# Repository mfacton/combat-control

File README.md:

# combat-control
All in one combat robot controller

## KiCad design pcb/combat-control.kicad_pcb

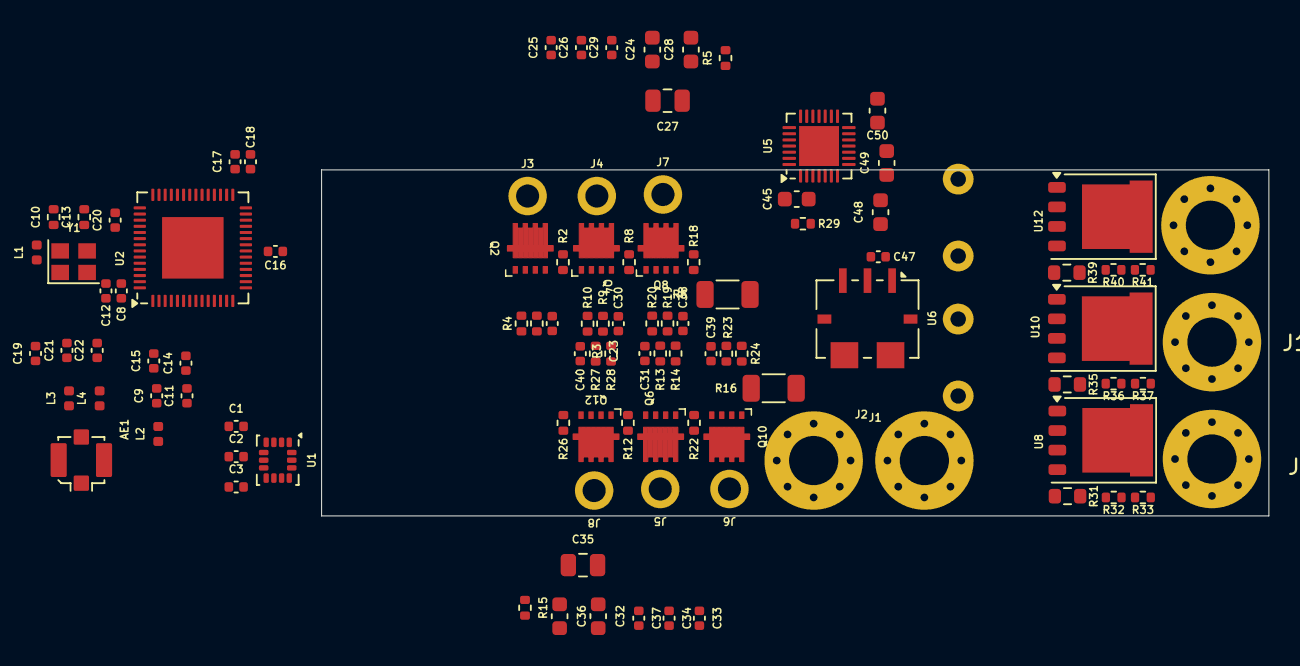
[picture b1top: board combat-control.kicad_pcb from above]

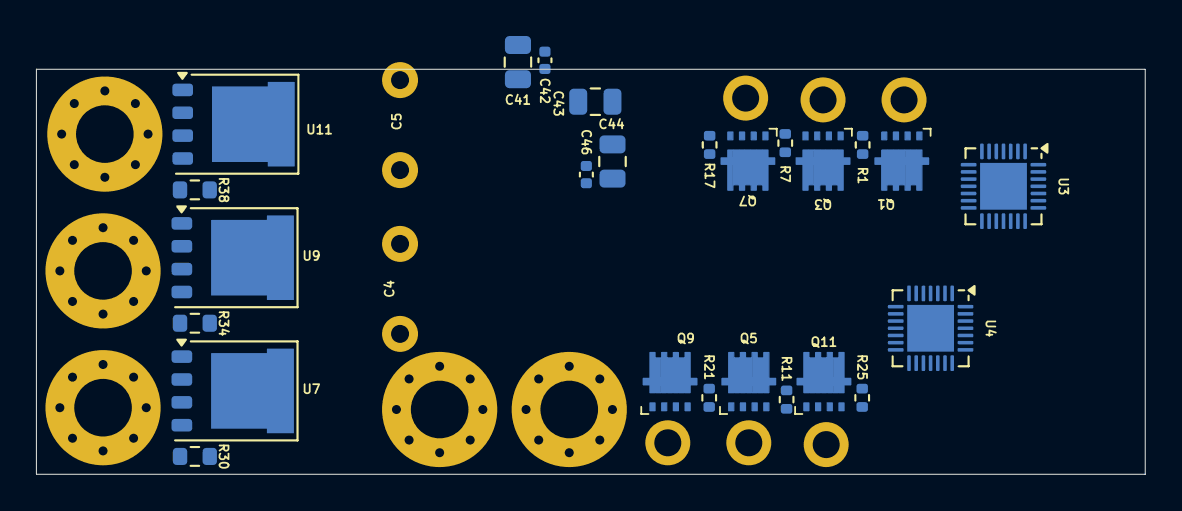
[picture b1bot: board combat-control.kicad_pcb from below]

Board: 4 copper layers, 61.6 x 22.5 mm, 130 parts (27 on the bottom side), 91 nets, no tracks yet.

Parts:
AE1: Antenna_Shield; U.FL_Molex_MCRF_73412-0110_Vertical
C1: 4u7; C_0402_1005Metric
C2, C3, C14, C15, C16, C17, C20, C25, C29, C33, C37, C42, C46, C47: 100n; C_0402_1005Metric
C4, C5: 2m2; C_D10xL16_Horizontal
C8, C11, C18, C23, C30, C31, C38, C39, C40: 1u; C_0402_1005Metric
C9: 10u; C_0402_1005Metric
C10, C13: C; R_0402_1005Metric
C12: 10n; C_0402_1005Metric
C19, C21, C22, C26, C34: C; C_0402_1005Metric
C24, C32, C48, C49, C50: 10u; C_0603_1608Metric
C27, C35, C43, C44: 10u; C_0805_2012Metric
C28, C36, C45: 470n; C_0603_1608Metric
C41: 22u; C_0805_2012Metric
J1, J2, J9, J10, J11: Conn_01x01_Pin; MountingHole_3.2mm_M3_Pad_Via
J3, J4, J5, J6, J7, J8: Conn_01x01_Pin; Pad-P1.5
L1, L3, L4: L; L_0402_1005Metric
L2: 2nH; L_0402_1005Metric
Q1, Q2, Q3, Q4, Q5, Q6, Q7, Q8, Q9, Q10, Q11, Q12: AON7544; DFN3x3A_8L_EP1_P
R1, R2, R7, R8, R11, R12, R17, R18, R21, R22, R25, R26: 22R; R_0402_1005Metric
R3, R9, R13, R19, R23, R27: 4k7; R_0402_1005Metric
R4, R10, R14, R20, R24, R28: 1k; R_0402_1005Metric
R5, R15: R; R_0402_1005Metric
R6, R16: 2m; R_1206_3216Metric
R29: 10k; R_0402_1005Metric
R30, R31, R34, R35, R38, R39: 22R; R_0603_1608Metric
R32, R36, R40: 15k; R_0402_1005Metric
R33, R37, R41: 2k; R_0402_1005Metric
U1: ICM-42688-P; LGA-14_3x2.5mm_P0.5mm_LayoutBorder3x4y
U2: ESP32-S3; QFN-56-1EP_7x7mm_P0.4mm_EP4x4mm
U3, U4, U5: DRV8328B; QFN-28-1EP_4x4mm_P0.4mm_EP2.6x2.6mm
U6: ACS781xLRTR-100B; Allegro_PSOF-7_4.8x6.4mm_P1.60mm
U7, U8, U9, U10, U11, U12: TPHR8504PL; PQFN-8-EP_6x5mm_P1.27mm_Generic
Y1: 40MHz; Crystal_SMD_2520-4Pin_2.5x2.0mm

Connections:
+3V3: C1.1, C2.1, C3.1, C8.1, C9.1, C11.1, C12.1, C14.1, C16.1, C17.1, C18.1, C20.1, C47.1, L2.1, U1.5 (VDDIO), U1.8 (VDD), U2.4 (CHIP_PU), U2.20 (VDD3P3_RTC), U2.29 (VDD_SPI), U2.46 (VDD3P3_CPU), U2.55 (VDDA), U2.56 (VDDA), U3.21 (INLC), U3.22 (INLB), U3.23 (INLA), U3.25 (~SLP), U4.21 (INLC), U4.22 (INLB), U4.23 (INLA), U4.25 (~SLP), U5.21 (INLC), U5.22 (INLB), U5.23 (INLA), U5.26 (DLVL), U6.1 (VCC)
/IFIG: U2.5 (GPIO0), U2.51 (GPIO45)
/ILIM: C26.1, C34.1, R5.1, R15.1
/LargeMotor/BSTA: C48.1, U5.5 (BSTA)
/LargeMotor/BSTB: C49.1, U5.9 (BSTB)
/LargeMotor/BSTC: C50.1, U5.13 (BSTC)
/LargeMotor/GVDD: C41.1, C42.1, U5.4 (GVDD)
/LargeMotor/HIA: R30.1, U5.7 (GHA)
/LargeMotor/HIB: R34.1, U5.11 (GHB)
/LargeMotor/HIC: R38.1, U5.15 (GHC)
/LargeMotor/LOA: R31.1, U5.8 (GLA)
/LargeMotor/LOB: R35.1, U5.12 (GLB)
/LargeMotor/LOC: R39.1, U5.16 (GLC)
/LargeMotor/LOW: C4.2, C5.1, U6.6 (IP-), U8.1 (S), U8.2 (S), U8.3 (S), U10.1 (S), U10.2 (S), U10.3 (S), U12.1 (S), U12.2 (S), U12.3 (S)
/LargeMotor/OUTA: C48.2, J9.1, R32.1, U5.6 (SHA), U7.1 (S), U7.2 (S), U7.3 (S), U8.5 (D)
/LargeMotor/OUTB: C49.2, J10.1, R36.1, U5.10 (SHB), U9.1 (S), U9.2 (S), U9.3 (S), U10.5 (D)
/LargeMotor/OUTC: C50.2, J11.1, R40.1, U5.14 (SHC), U11.1 (S), U11.2 (S), U11.3 (S), U12.5 (D)
/SNSA1: R3.2, R4.1
/SNSA2: R23.2, R24.1
/SNSA3: R32.2, R33.1
/SNSB1: R9.2, R10.1
/SNSB2: R13.2, R14.1
/SNSB3: R36.2, R37.1
/SNSC1: R19.2, R20.1
/SNSC2: R27.2, R28.1
/SNSC3: R40.2, R41.1
/STP: U2.8 (GPIO3), U2.52 (GPIO46)
/SmallMotor1/BSTA: C23.1, U3.5 (BSTA)
/SmallMotor1/BSTB: C30.1, U3.9 (BSTB)
/SmallMotor1/BSTC: C38.1, U3.13 (BSTC)
/SmallMotor1/DL: R5.2, U3.26 (DLVL)
/SmallMotor1/GVDD: C24.1, C25.1, U3.4 (GVDD)
/SmallMotor1/HIA: R1.1, U3.7 (GHA)
/SmallMotor1/HIB: R7.1, U3.11 (GHB)
/SmallMotor1/HIC: R17.1, U3.15 (GHC)
/SmallMotor1/LOA: R2.1, U3.8 (GLA)
/SmallMotor1/LOB: R8.1, U3.12 (GLB)
/SmallMotor1/LOC: R18.1, U3.16 (GLC)
/SmallMotor1/LOW: Q2.1 (S), Q2.2 (S), Q2.3 (S), Q4.1 (S), Q4.2 (S), Q4.3 (S), Q8.1 (S), Q8.2 (S), Q8.3 (S), R6.1, U3.17 (LSS)
/SmallMotor1/OUTA: C23.2, J3.1, Q1.1 (S), Q1.2 (S), Q1.3 (S), Q2.5 (D), Q2.6 (D), Q2.7 (D), Q2.8 (D), R3.1, U3.6 (SHA)
/SmallMotor1/OUTB: C30.2, J4.1, Q3.1 (S), Q3.2 (S), Q3.3 (S), Q4.5 (D), Q4.6 (D), Q4.7 (D), Q4.8 (D), R9.1, U3.10 (SHB)
/SmallMotor1/OUTC: C38.2, J7.1, Q7.1 (S), Q7.2 (S), Q7.3 (S), Q8.5 (D), Q8.6 (D), Q8.7 (D), Q8.8 (D), R19.1, U3.14 (SHC)
/SmallMotor2/BSTA: C39.1, U4.5 (BSTA)
/SmallMotor2/BSTB: C31.1, U4.9 (BSTB)
/SmallMotor2/BSTC: C40.1, U4.13 (BSTC)
/SmallMotor2/DL: R15.2, U4.26 (DLVL)
/SmallMotor2/GVDD: C32.1, C33.1, U4.4 (GVDD)
/SmallMotor2/HIA: R21.1, U4.7 (GHA)
/SmallMotor2/HIB: R11.1, U4.11 (GHB)
/SmallMotor2/HIC: R25.1, U4.15 (GHC)
/SmallMotor2/LOA: R22.1, U4.8 (GLA)
/SmallMotor2/LOB: R12.1, U4.12 (GLB)
/SmallMotor2/LOC: R26.1, U4.16 (GLC)
/SmallMotor2/LOW: Q6.1 (S), Q6.2 (S), Q6.3 (S), Q10.1 (S), Q10.2 (S), Q10.3 (S), Q12.1 (S), Q12.2 (S), Q12.3 (S), R16.1, U4.17 (LSS)
/SmallMotor2/OUTA: C39.2, J6.1, Q9.1 (S), Q9.2 (S), Q9.3 (S), Q10.5 (D), Q10.6 (D), Q10.7 (D), Q10.8 (D), R23.1, U4.6 (SHA)
/SmallMotor2/OUTB: C31.2, J5.1, Q5.1 (S), Q5.2 (S), Q5.3 (S), Q6.5 (D), Q6.6 (D), Q6.7 (D), Q6.8 (D), R13.1, U4.10 (SHB)
/SmallMotor2/OUTC: C40.2, J8.1, Q11.1 (S), Q11.2 (S), Q11.3 (S), Q12.5 (D), Q12.6 (D), Q12.7 (D), Q12.8 (D), R27.1, U4.14 (SHC)
/VDD3: C15.1, L2.2, U2.2 (VDD3P3), U2.3 (VDD3P3)
GND: AE1.2 (Shield), C1.2, C2.2, C3.2, C8.2, C9.2, C10.2, C11.2, C12.2, C13.2, C14.2, C15.2, C16.2, C17.2, C18.2, C19.2, C20.2, C21.2, C22.2, C24.2, C25.2, C26.2, C27.2, C29.2, C32.2, C33.2, C34.2, C35.2, C37.2, C41.2, C42.2, C43.2, C44.2, C46.2, C47.2, J2.1, R4.2, R6.2, R10.2, R14.2, R16.2, R20.2, R24.2, R28.2, R29.2, R33.2, R37.2, R41.2, U1.6 (GND), U1.7 (RESV), U1.11 (RESV), U2.57 (GND), U3.27 (DT), U3.28 (GND), U3.29 (PAD), U4.27 (DT), U4.28 (GND), U4.29 (PAD), U5.17 (LSS), U5.28 (GND), U5.29 (PAD), U6.2 (GND), U6.5 (IP+), Y1.2, Y1.4
unnamed: AE1.1 (A), C21.1, L3.2, L4.1
unnamed: C10.1, L1.1, Y1.1
unnamed: C22.1, L4.2
unnamed: Q1.4 (G), R1.2
unnamed: Q2.4 (G), R2.2
unnamed: Q3.4 (G), R7.2
unnamed: Q4.4 (G), R8.2
unnamed: Q5.4 (G), R11.2
unnamed: Q6.4 (G), R12.2
unnamed: Q7.4 (G), R17.2
unnamed: Q8.4 (G), R18.2
unnamed: Q9.4 (G), R21.2
unnamed: Q10.4 (G), R22.2
unnamed: Q11.4 (G), R25.2
unnamed: Q12.4 (G), R26.2
unnamed: C19.1, L3.1, U2.1 (LNA_IN)
unnamed: C13.1, U2.53 (XTAL_N), Y1.3
unnamed: L1.2, U2.54 (XTAL_P)
unnamed: C28.2, U3.3 (CPH)
unnamed: C28.1, U3.2 (CPL)
unnamed: C36.2, U4.3 (CPH)
unnamed: C36.1, U4.2 (CPL)
unnamed: C45.2, U5.3 (CPH)
unnamed: C45.1, U5.2 (CPL)
unnamed: R29.1, U5.27 (DT)
unnamed: R30.2, U7.4 (G)
unnamed: R31.2, U8.4 (G)
unnamed: R34.2, U9.4 (G)
unnamed: R35.2, U10.4 (G)
unnamed: R38.2, U11.4 (G)
unnamed: R39.2, U12.4 (G)
VDD: C4.1, C5.2, C27.1, C29.1, C35.1, C37.1, C43.1, C44.1, C46.1, J1.1, Q1.5 (D), Q1.6 (D), Q1.7 (D), Q1.8 (D), Q3.5 (D), Q3.6 (D), Q3.7 (D), Q3.8 (D), Q5.5 (D), Q5.6 (D), Q5.7 (D), Q5.8 (D), Q7.5 (D), Q7.6 (D), Q7.7 (D), Q7.8 (D), Q9.5 (D), Q9.6 (D), Q9.7 (D), Q9.8 (D), Q11.5 (D), Q11.6 (D), Q11.7 (D), Q11.8 (D), U3.1 (PVDD), U4.1 (PVDD), U5.1 (PVDD), U7.5 (D), U9.5 (D), U11.5 (D)

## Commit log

2024-11-30 Init project
2024-11-30 Select parts
2024-12-01 Save progress
2024-12-01 Save test layout
2024-12-02 Save layout
